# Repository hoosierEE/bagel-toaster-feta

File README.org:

* BB Triple Combo
KiCad projects files for a 3-in-1 effect pedal:
1. boost
2. overdrive/distoriton
3. fuzzy octave up

Each of these circuits is an original analog design by me.
Each effect can be independently engaged or bypassed via 3 footswitches, and there is a toggle to change the order of the boost (first or last) so you can have either:

#+begin_src 
boost → distortion → octave
#+end_src
 
or:

#+begin_src 
distortion → octave → boost 
#+end_src

Finally, there is a "sag" control to starve the pedal of power. No idea what that will sound like yet as I've not even prototyped it. In theory it should increase distortion and maybe add some subtle compression type effect.

Called "BB Triple Combo" because the overall design was at the request of an internet friend with these initials.

** Boost
Despite having the most clipping diodes of any effect in this bundle, the boost is clean-ish. It's a non-inverting op-amp based boost with LEDs in the feedback loop (like a Tube Screamer) but the gain is dept low so these diodes rarely have an effect. Their purpose is mostly to prevent the opamp from clipping on large inputs. After the op-amp, there is also a diodes-to-ground clipping section, similar to an MXR Distortion+ effect. But rather than causing distortion, these diodes add a supposedly tube-like smidge of dynamic harmonic content. Credit for this concept goes to the wizards at RunOffGroove and their [[https://www.runoffgroove.com/thunderbird.html][Thunderbird]] design.

[[file:./bagel.png]]

Controls:
- gain

** Distortion
This distortion design eschews most guitar distortion design sensibilities. The signal path starts with a high-impedance buffer to preserve your guitar's high frequencies. Next comes an inverting soft clipping stage with a unique voltage divider gain control. This gain control arrangement permits a wide range of gain adjustment (11dB-40dB) despite using a mere 50k potentiometer in the feedback loop (lower resistance means less thermal noise).

#+begin_quote
One note regarding the schematic. The current-limiting resistor in series with the clipping diodes can be anywhere from 1k to 10k depending on mood. The original value (10k) encourages a softer clipping sound whereas lower values down to 1k will be harsher and more aggressive.
#+end_quote

[[file:./toaster.png]]

From there the signal goes through a 2nd-order lowpass filter with a range of adjustment from 500Hz to 2.6kHz. This isn't a large range of sweep but the 12dB/octave slope makes it feel like it covers more sonic ground. This kind of filter is more typically found on analog synthesizer equipment, but I think it works well for guitar.

Controls from left to right:
- volume
- filter
- gain

** Octave Fuzz
This effect started as an experiment in making a "squarer" circuit. Up front is a JFET buffer and two high-gain CMOS inverter stages. The squarer concept is realized by splitting this amplified signal into two paths and routing each through a pair of series diodes pointed in opposite directions. The negative signal routes straight into the output mixer, while the positive signal gets inverted and then routes through an adjustable potentiometer labeled "Splat" and some series resistance and capacitance. The Splat control allows you to adjust the character of the octave effect - more pronounced octave in one direction, and more compressed and spongy in the other direction.

[[file:./feta.png]]

Controls from top to bottom:
- volume
- splat

* Circuit Board Layout
This is the largest design I've made in KiCad's PCB layout tool to date and I was proud of getting all the traces on a single layer.

[[file:./1590xx-layout.png]]

Eventually I changed to dual layer because it let me make the board more compact and route some traces more cleanly.
[[file:./bbtc-layout.png]]

KiCad is quirky and frustrating at first, but it's growing on me. The 3d rendering tool is especially cool.

[[file:./bbtc-back.png]]
[[file:./bbtc-front.png]]

# [[file:./btf-render-back.png]]
# [[file:./btf-render-front.png]]

+Next step is to have the board fabricated. I used OSH Park last time and the results were good but not fast. Might try a different one this time.+

Currently being fabbed by OSH Park. Hope it turns out as good as the last board.

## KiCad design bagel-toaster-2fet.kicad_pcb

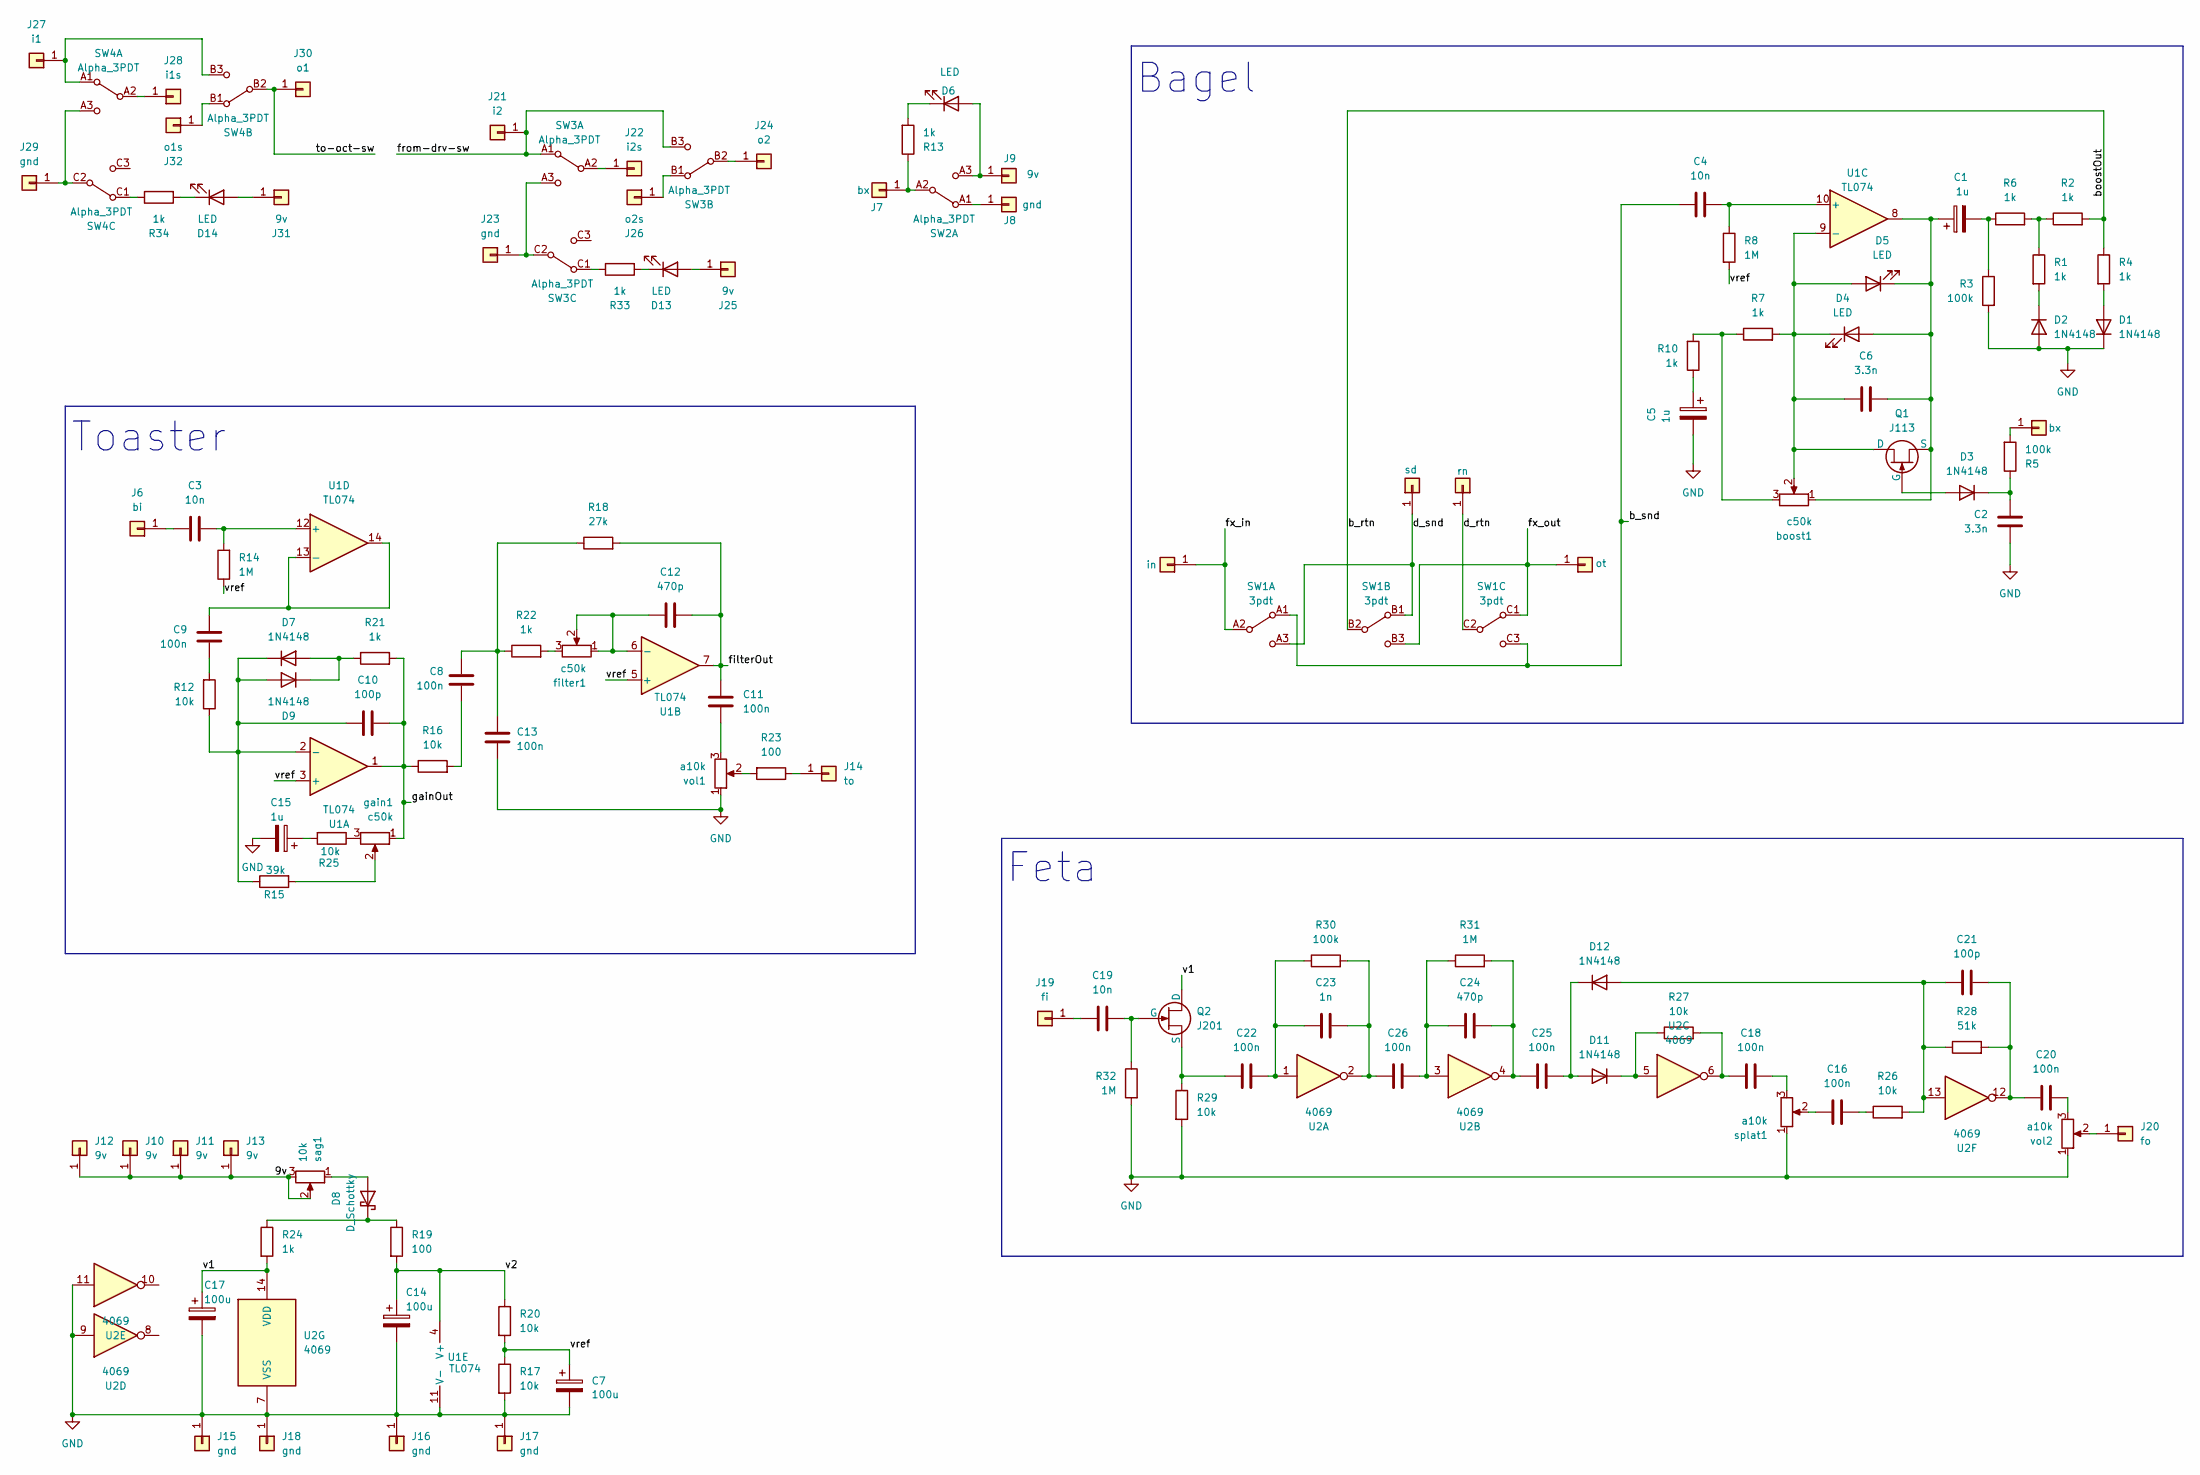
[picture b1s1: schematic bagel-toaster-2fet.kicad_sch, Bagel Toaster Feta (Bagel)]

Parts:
C1, C5, C15: 1u; CP_ELCO_1x2_S
C2, C6: 3.3n; C_CERAMIC_1x2
C3, C4, C19: 10n; C_CERAMIC_1x2
C7, C14, C17: 100u; CP_ELCO_1x2_S
C8, C9, C11, C13, C16, C18, C20, C22, C25, C26: 100n; C_CERAMIC_1x2
C10, C21: 100p; C_CERAMIC_1x2
C12, C24: 470p; C_CERAMIC_1x2
C23: 1n; C_CERAMIC_1x2
D1, D2, D3, D7, D9, D11, D12: 1N4148; D_DO-35_SOD27_P7.62mm_Horizontal
D4, D5, D6, D13, D14: LED; LED_3.0mm
D8: D_Schottky; D_A-405_P7.62mm_Horizontal
J1, J7: bx; SolderWire-0.5sqmm_1x01_D0.9mm_OD2.1mm
J2: do_snd; SolderWire-0.5sqmm_1x01_D0.9mm_OD2.1mm
J3: out; SolderWire-0.5sqmm_1x01_D0.9mm_OD2.1mm
J4: in; SolderWire-0.5sqmm_1x01_D0.9mm_OD2.1mm
J5: do_rtn; SolderWire-0.5sqmm_1x01_D0.9mm_OD2.1mm
J6: bi; SolderWire-0.5sqmm_1x01_D0.9mm_OD2.1mm
J8, J15, J16, J17, J18, J23, J29: gnd; SolderWire-0.5sqmm_1x01_D0.9mm_OD2.1mm
J9, J10, J11, J12, J13, J25, J31: 9v; SolderWire-0.5sqmm_1x01_D0.9mm_OD2.1mm
J14: to; SolderWire-0.5sqmm_1x01_D0.9mm_OD2.1mm
J19: fi; SolderWire-0.5sqmm_1x01_D0.9mm_OD2.1mm
J20: fo; SolderWire-0.5sqmm_1x01_D0.9mm_OD2.1mm
J21: i2; SolderWire-0.5sqmm_1x01_D0.9mm_OD2.1mm
J22: i2s; SolderWire-0.5sqmm_1x01_D0.9mm_OD2.1mm
J24: o2; SolderWire-0.5sqmm_1x01_D0.9mm_OD2.1mm
J26: o2s; SolderWire-0.5sqmm_1x01_D0.9mm_OD2.1mm
J27: i1; SolderWire-0.5sqmm_1x01_D0.9mm_OD2.1mm
J28: i1s; SolderWire-0.5sqmm_1x01_D0.9mm_OD2.1mm
J30: o1; SolderWire-0.5sqmm_1x01_D0.9mm_OD2.1mm
J32: o1s; SolderWire-0.5sqmm_1x01_D0.9mm_OD2.1mm
Q1: J113; TO-92_W
Q2: J201; TO-92_W
R1, R2, R4, R6, R7, R10, R13, R21, R22, R24, R33, R34: 1k; R_1x4
R3, R5, R30: 100k; R_1x4
R8, R14, R31, R32: 1M; R_1x4
R12, R16, R17, R20, R25, R26, R27, R29: 10k; R_1x4
R15: 39k; R_1x4
R18: 27k; R_1x4
R19, R23: 100; R_1x4
R28: 51k; R_1x4
SW1: 3pdt; 3pdt-toggle
SW2, SW3, SW4: Alpha_3PDT; 3pdt
U1: TL074; DIP-14_W7.62mm
U2: 4069; DIP-14_W7.62mm
boost1: c50k; pot-16mm-short-leg
filter1: c50k; pot-16mm-short-leg
gain1: c50k; pot-16mm-short-leg
sag1: 10k; Potentiometer_Alpha_RD901F-40-00D_Single_Vertical
splat1: a10k; pot-16mm-short-leg
vol1, vol2: a10k; pot-16mm-short-leg

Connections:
/9v: J10.1, J11.1, J12.1, J13.1, sag1.2, sag1.3
/b_rtn: R2.2, R4.1, SW1.B2
/b_snd: C4.1, SW1.A1, SW1.C3
/d_rtn: J5.1, SW1.C2
/d_snd: J2.1, SW1.A3, SW1.B1
/filterOut: C11.1, C12.2, R18.2, U1.7
/from-drv-sw: J21.1, SW3.A1, SW3.B3
/fx_in: J4.1, SW1.A2
/fx_out: J3.1, SW1.B3, SW1.C1
/gainOut: C10.2, R16.1, R21.2, U1.1, gain1.1
/to-oct-sw: J30.1, SW4.B2
/v1: C17.1, Q2.1 (D), R24.2, U2.14 (VDD)
/v2: C14.1, R19.2, R20.1, U1.4 (V+)
/vref: C7.1, R8.2, R14.1, R17.1, R20.2, U1.3 (+), U1.5 (+)
GND: C2.1, C5.2, C7.2, C13.1, C14.2, C15.2, C17.2, D1.1 (K), D2.2 (A), J15.1, J16.1, J17.1, J18.1, R3.2, R17.2, R29.2, R32.2, U1.11 (V-), U2.7 (VSS), U2.9, U2.11, splat1.1, vol1.1, vol2.1
unnamed: C1.2, R3.1, R6.1
unnamed: C5.1, R10.1
unnamed: C8.2, R16.2
unnamed: C9.1, R12.2
unnamed: C11.2, vol1.3
unnamed: C8.1, C13.2, R18.1, R22.1
unnamed: C15.1, R25.2
unnamed: C16.1, R26.1
unnamed: C16.2, splat1.2
unnamed: C18.1, R27.2, U2.6
unnamed: C18.2, splat1.3
unnamed: C20.1, C21.2, R28.2, U2.12
unnamed: C20.2, vol2.3
unnamed: C22.2, C23.1, R30.1, U2.1
unnamed: C23.2, C26.1, R30.2, U2.2
unnamed: C24.1, C26.2, R31.1, U2.3
unnamed: C24.2, C25.1, R31.2, U2.4
unnamed: D1.2 (A), R4.2
unnamed: D2.1 (K), R1.2
unnamed: D3.2 (A), Q1.2 (G)
unnamed: C2.2, D3.1 (K), R5.1
unnamed: C1.1, C6.2, D4.2 (A), D5.1 (K), Q1.3 (S), U1.8, boost1.1
unnamed: C6.1, D4.1 (K), D5.2 (A), Q1.1 (D), R7.2, U1.9 (-), boost1.2
unnamed: D6.2 (A), J9.1, SW2.A3
unnamed: D6.1 (K), R13.2
unnamed: D7.2 (A), D9.1 (K), R21.1
unnamed: C10.1, D7.1 (K), D9.2 (A), R12.1, R15.1, U1.2 (-)
unnamed: D8.2 (A), sag1.1
unnamed: D8.1 (K), R19.1, R24.1
unnamed: C25.2, D11.2 (A), D12.1 (K)
unnamed: D11.1 (K), R27.1, U2.5
unnamed: C21.1, D12.2 (A), R26.2, R28.1, U2.13
unnamed: D13.2 (A), J25.1
unnamed: D13.1 (K), R33.2
unnamed: D14.2 (A), J31.1
unnamed: D14.1 (K), R34.2
unnamed: J1.1, R5.2
unnamed: C3.1, J6.1
unnamed: J7.1, R13.1, SW2.A2
unnamed: J8.1, SW2.A1
unnamed: J14.1, R23.1
unnamed: C19.1, J19.1
unnamed: J20.1, vol2.2
unnamed: J22.1, SW3.A2
unnamed: J23.1, SW3.A3, SW3.C2
unnamed: J24.1, SW3.B2
unnamed: J26.1, SW3.B1
unnamed: J27.1, SW4.A1, SW4.B3
unnamed: J28.1, SW4.A2
unnamed: J29.1, SW4.A3, SW4.C2
unnamed: J32.1, SW4.B1
unnamed: C19.2, Q2.2 (G), R32.1
unnamed: C22.1, Q2.3 (S), R29.1
unnamed: R1.1, R2.1, R6.2
unnamed: R7.1, R10.2, boost1.3
unnamed: R15.2, gain1.2
unnamed: R22.2, filter1.3
unnamed: R23.2, vol1.2
unnamed: R25.1, gain1.3
unnamed: R33.1, SW3.C1
unnamed: R34.1, SW4.C1
unnamed: C12.1, U1.6 (-), filter1.1, filter1.2
unnamed: C4.2, R8.1, U1.10 (+)
unnamed: C3.2, R14.2, U1.12 (+)
unnamed: C9.2, U1.13 (-), U1.14

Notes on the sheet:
Toaster
Bagel
Feta

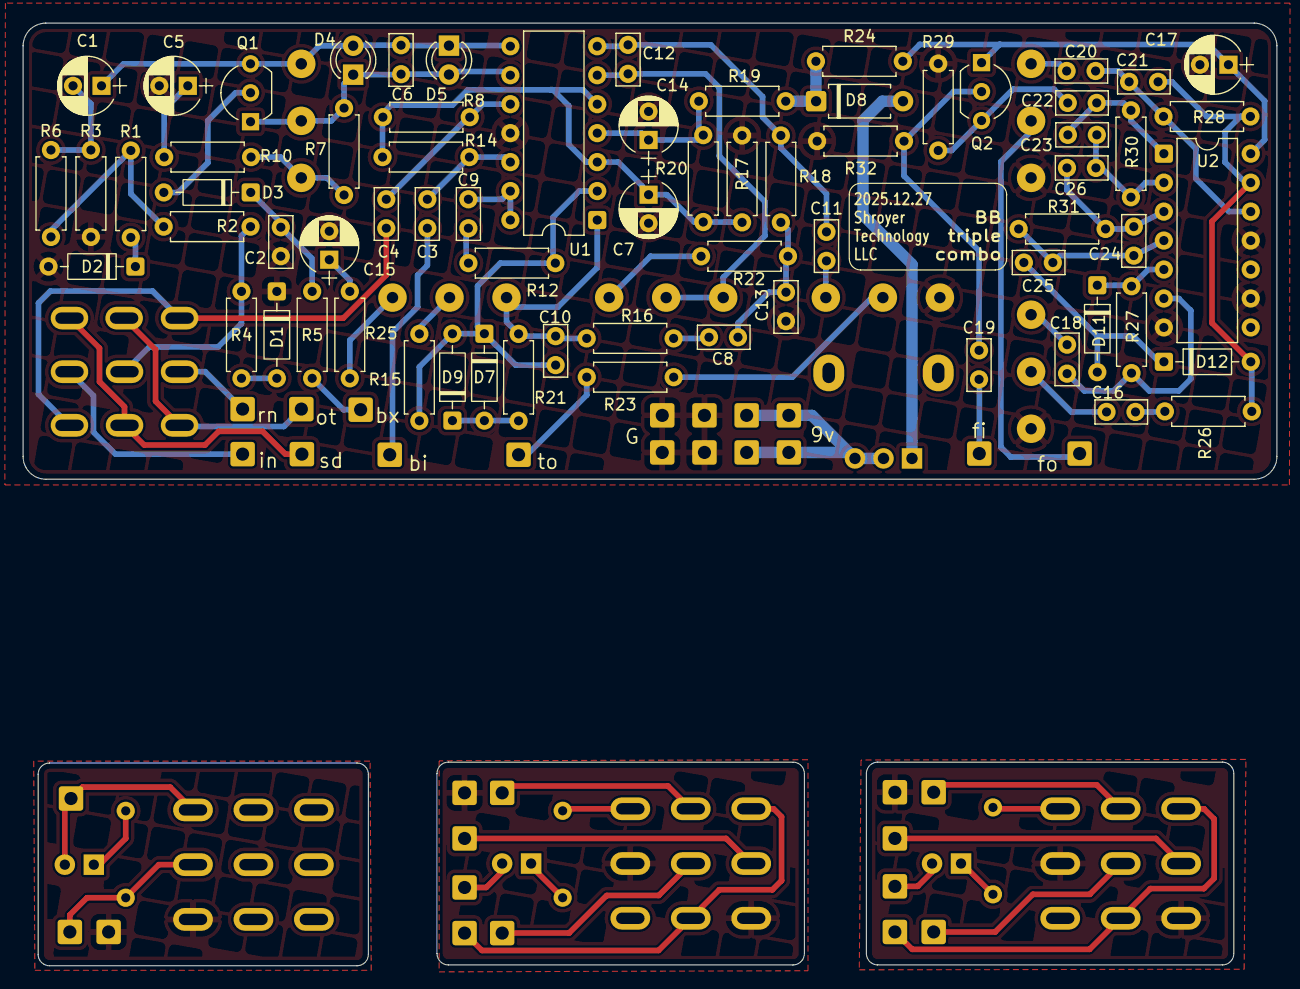
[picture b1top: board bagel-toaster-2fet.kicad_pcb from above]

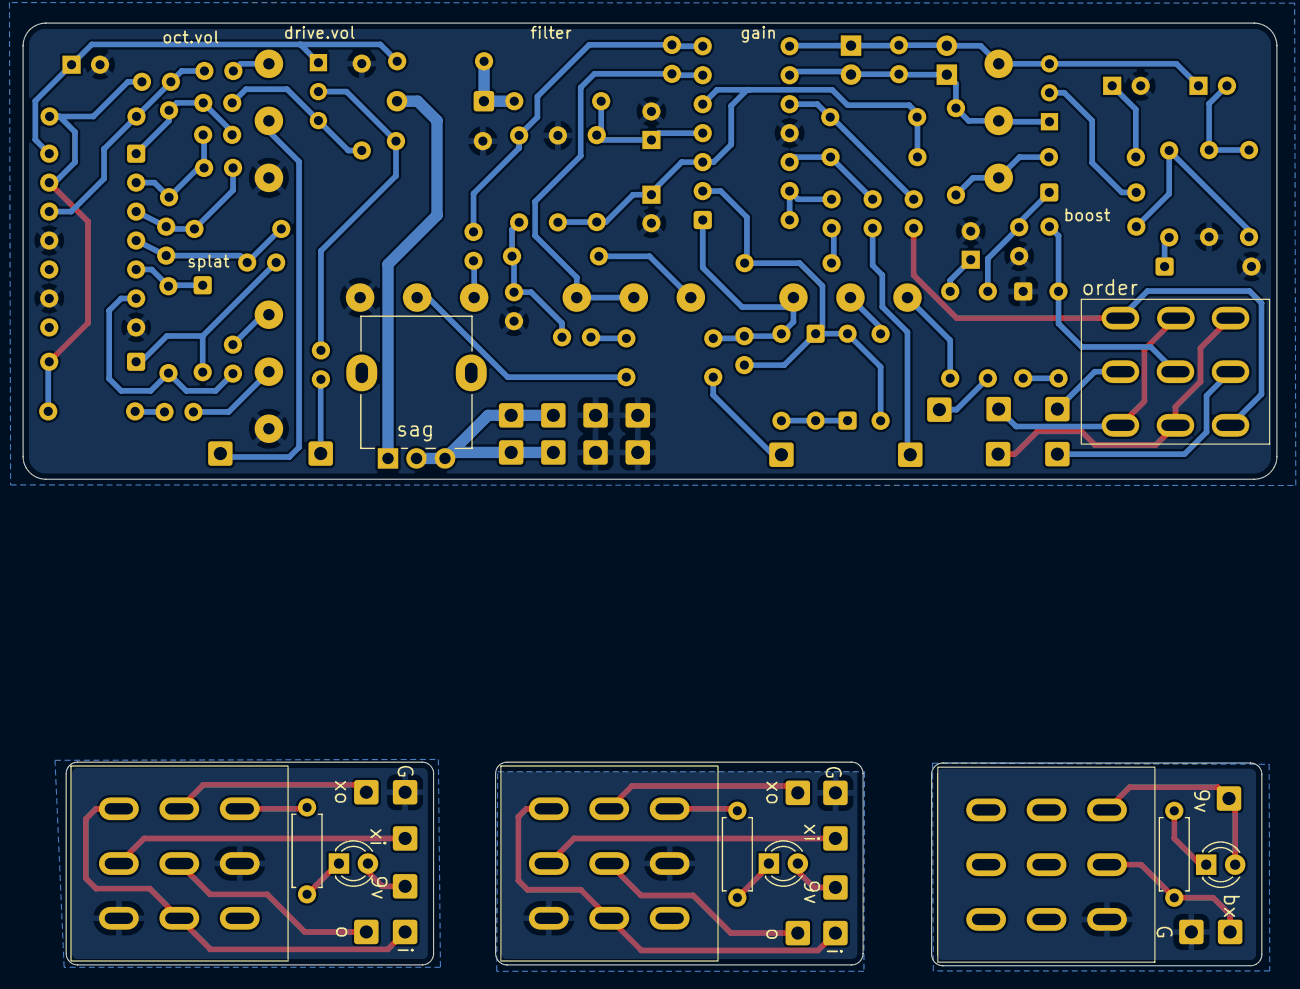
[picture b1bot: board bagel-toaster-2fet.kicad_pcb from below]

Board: 2 copper layers, 110.0 x 82.7 mm, 118 parts (32 on the bottom side), 80 nets.

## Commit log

2026-01-02 Create LICENSE
2026-01-02 add design notes
2026-01-02 add sag control and reannotate
2026-01-02 more gitignore for KiCad
2026-01-03 update annotations
2026-01-03 16mm pot refactor done
2026-01-12 one sided and smaller
2026-01-14 tidier
2026-02-03 smaller
2026-02-15 looking pretty good
2026-02-17 1590dd
2026-02-17 update layout for 1590xx
2026-02-17 oops add images
2026-02-17 remove old images
2026-02-27 fabbed
2026-02-27 update readme after fab
2026-02-27 oh yeah save
2026-02-27 mention sag
2026-02-27 note current limiting resistor
